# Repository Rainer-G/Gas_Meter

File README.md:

# Gas Verbrauch messen und verarbeiten 

## Funktion

Manche Gaszähler geben pro vebrauchte 10 Liter einen magnetischen Impuls ab.
Dieser Impuls wird mit einem Hall Sensor in elektrische Impulse gewandelt, ein RTC Baustein PCF8583 arbeitet als Zähler und speichert die Zahl der Impulse im internen RAM ab.

PCB Eagle Dateien und Stückliste anbei.

Die Daten werden mit Hilfe eines ESP8266 über die I²C SAchnittstelle ausgelesen und verarbeitet. 
Über das MQTT Protokoll werden die Daten an einen lokalen Broker weitergeleitet, Daten werden nicht ins Internet hochgeladen.
Eine 3 Volt Knopfzelle versorgt den Baustein mit Energie und erhält die Daten bei Stromausfall.

* Diese Daten werden im RTC RAM gespeichert

1. Zählimpulse
2. Zählerstand zu Beginn der Messung ( Counts = 0 )
3. Zählerstand zu Beginn der Abrechnungsperiod
4. monatlicherVerbrauch in m³
5. Datum und Uhrzeit des letzen Auslesens des RTC Bausteins

* Diese Daten werden über MQTT an den Broker gesendet

1. Uhrzeit 
2. Gesamtverbrauch in kWh
3. Verbrauch zwischen zwei Zugriffen auf den RTC Speicher in kWh
4. Anzahl der Impulse seit Reset
5. Gesamtverbrauch in m³
6. Zählerstand zum Begin der Messung ( Counts = 0 ) in Liter
7. Zählerstand zum Begin der Abrechnungsperiode in Liter
8. nach Bedarf monatlicher Verbrauch
9. Status ( OK wenn Zugriff auf den RTC Baustein möglich )

* Diese Daten/Kommandos können vom Broker an den ESP8266 gesendet werden

1. Publish consumption of a single month or month 1 to 12 
 * SYNTAX  : "Energy/Test/command"
 * PAYLOAD : "Month, x"
 * value for x : either 1 to 12 for a single month, x > 12 shows all 12 months
  
 2. Set consumption for the start of a heating period 
 * SYNTAX  : "Energy/Test/command"
 * PAYLOAD : "InitP, x"
 * value for x : consumption in liter

 3. Set initial consumption value for a count value of zero 
 * SYNTAX  : "Energy/Test/command"
 * PAYLOAD : "InitS, x"
 * value for x : consumption in liter

 4. Set consumption for a single month to init data  
 * SYNTAX  : "Energy/Test/command"
 * PAYLOAD : "InitM, x ; y"
 * value for x : selected month
 * value for y : consumption in liter
 
 5. Set consumption for the start of a counting period 
 * Initialyse RTC chip and set initial consumption value for count = 0 of a counting period 
 * SYNTAX  : "Energy/Test/command"
 * PAYLOAD : "InitC, x"
 * value for x : consumption in liter

## Vorbereitung

* in Gas_WiFi SSID und Passwort eintragen
* in Gas_MQTT IP Adresse des MQTT Broker eintragen
* ggfs. Thinkspeak aktivieren und Channel und Key eintragen
* Topic für MQTT an die eigenen Wünsche anpassen

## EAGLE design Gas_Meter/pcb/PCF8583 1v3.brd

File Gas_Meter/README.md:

# Gas_Meter
 Read Gas Consumption with hall effect sensor and process with ESP8266

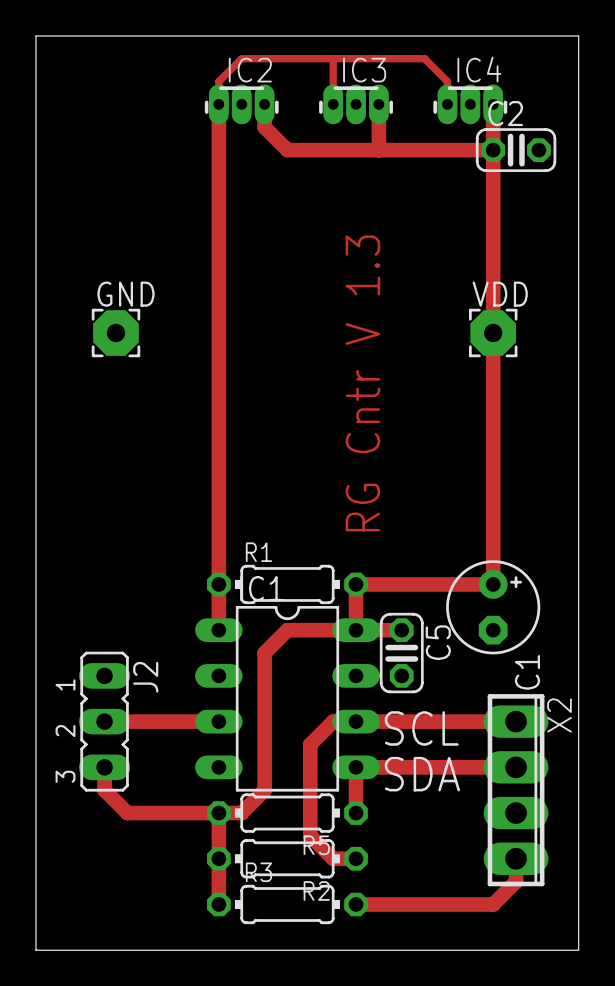
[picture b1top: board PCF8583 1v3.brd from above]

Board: 2 copper layers, 30.1 x 50.8 mm, 15 parts (0 on the bottom side), 7 nets.

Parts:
C1: 47µF; E2,5-5
C2, C5: 10nF; C025-024X044
GND: 2,54/1,0
IC1: PCF8583P; DIL08
IC2, IC3, IC4: A1301UA; SIP3-UA
J2: JP2
R1: 470k; 0204/7
R2, R5: 220k; 0204/7
R3: 10k; 0204/7
VDD: 2,54/1,0
X2: 4POL254

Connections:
CNT: IC1.1, IC2.3, IC3.3, IC4.3, R1.1
GND: C1.-, C2.2, C5.2, GND.1, IC1.4, IC2.2, IC3.2, IC4.2, J2.1, X2.3
unnamed: R3.2, X2.4
unnamed: IC1.3, J2.2
SCL: IC1.6, R2.1, X2.1
SDA: IC1.5, R5.1, X2.2
VDD: C1.+, C2.1, C5.1, IC1.8, IC2.1, IC3.1, IC4.1, J2.3, R1.2, R2.2, R3.1, R5.2, VDD.1

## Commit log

2023-09-08 Update README.md
    Funktion und Daten ergänzt
2023-09-08 Add files via upload
    Added Text for Jumper 2
2023-09-08 Added Text for Jumper J2
2023-09-10 Bug Fix in Init
